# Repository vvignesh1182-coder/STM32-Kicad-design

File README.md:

# STM32 2-Layer PCB Design

A custom 2-layer Printed Circuit Board (PCB) designed around the STM32 microcontroller. This repository contains the complete open-source hardware files, schematics, PCB layouts, and manufacturing outputs created using **KiCad**.

---

## 📌 Project Overview
This project focuses on robust hardware layout practices for embedded microcontrollers, featuring optimized power distribution, ground copper pour zones, and signal integrity routing tailored for a standard 2-layer manufacturing stackup.

---

## 🚀 Key Features
* **Microcontroller Core:** Built around the STM32 MCU family for high-performance embedded control.
* **Power & Filtering:** Stable regulated power distribution featuring $+3.3\text{V}$ traces and ferrite bead isolation (`FB1`) to minimize noise between digital and analog domains.
* **Copper Ground Pour:** Utilizes dedicated GND copper fill zones and ground stitching vias to ensure low-impedance return paths and mitigate EMI.
* **Design Verification:** Fully verified and DRC-clean (Design Rules Checker) with confirmed schematic-to-layout parity.

---

## 📂 Repository Structure
```text
├── Schematic/       # KiCad schematic files (.kicad_sch) and symbol libraries
├── PCB/             # Board layout files (.kicad_pcb) and stackup settings
├── Manufacturing/   # Gerber files, drill files, and Bill of Materials (BOM) for fabrication
└── README.md        # Project documentation

🛠️ Tools & Requirements
Design Software: KiCad (v8.0 or compatible version recommended)

⚙️ Getting Started
Clone the repository:

Bash
git clone [https://github.com/vvignesh1182-coder/STM32-Kicad-design.git](https://github.com/vvignesh1182-coder/STM32-Kicad-design.git)
Open KiCad, select File > Open Project, and choose the .kicad_pro file from the repository directory.

Explore the Schematic Editor or PCB Editor to inspect the routing, stackup, and component placement.

📦 Manufacturing Outputs
The Manufacturing/ folder contains all necessary files ready to be zipped and uploaded directly to standard PCB fabrication houses (such as JLCPCB or PCBWay):

Gerber files (Copper layers, silkscreen, mask, edge cuts)

Excellon Drill files

Bill of Materials (BOM) CSV file

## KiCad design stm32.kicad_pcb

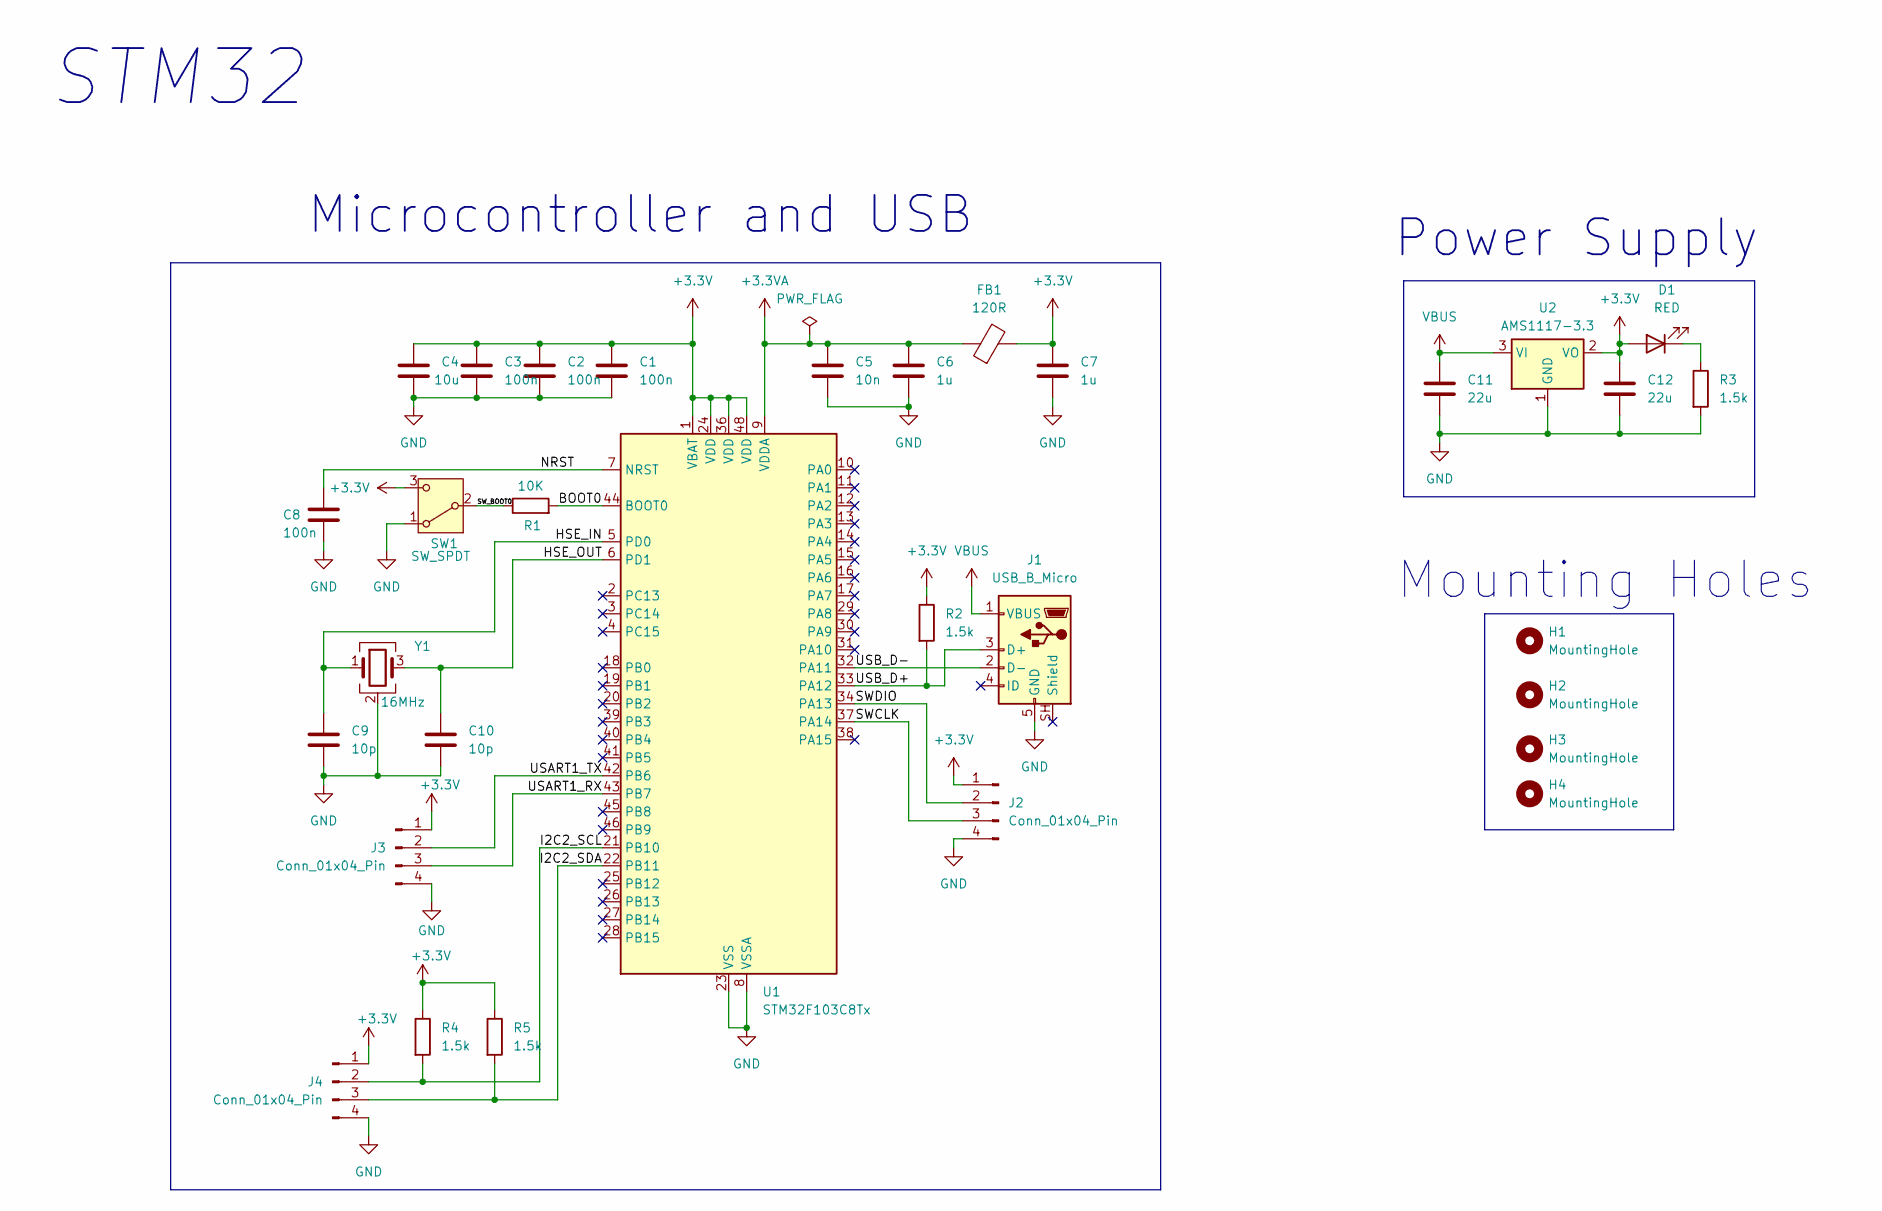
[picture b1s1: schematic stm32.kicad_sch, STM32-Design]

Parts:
C1, C2, C3, C8: 100n; C_0402_1005Metric
C4: 10u; C_0603_1608Metric
C5: 10n; C_0603_1608Metric
C6, C7: 1u; C_0402_1005Metric
C9, C10: 10p; C_0402_1005Metric
C11, C12: 22u; C_0805_2012Metric
D1: RED; LED_0603_1608Metric
FB1: 120R; L_0201_0603Metric
H1, H2, H3, H4: MountingHole; MountingHole_2.2mm_M2
J1: USB_B_Micro; USB_Micro-B_Wuerth_629105150521
J2, J3, J4: Conn_01x04_Pin; PinHeader_1x04_P2.54mm_Vertical
R1: 10K; R_0402_1005Metric
R2, R3, R4, R5: 1.5k; R_0402_1005Metric
SW1: SW_SPDT; SW_Slide_SPDT_Angled_CK_OS102011MA1Q
U1: STM32F103C8Tx; LQFP-48_7x7mm_P0.5mm
U2: AMS1117-3.3; SOT-223-3_TabPin2
Y1: 16MHz; Crystal_SMD_3225-4Pin_3.2x2.5mm

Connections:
+3.3V: C1.2, C2.2, C3.2, C4.2, C7.1, C12.1, D1.2 (A), FB1.2, J2.1, J3.1, J4.1, R2.1, R4.1, R5.1, SW1.3 (C), U1.1 (VBAT), U1.24 (VDD), U1.36 (VDD), U1.48 (VDD), U2.2 (VO)
+3.3VA: C5.1, C6.1, FB1.1, U1.9 (VDDA)
/BOOT0: R1.2, U1.44 (BOOT0)
/HSE_IN: C9.1, U1.5 (PD0), Y1.1
/HSE_OUT: C10.1, U1.6 (PD1), Y1.3
/I2C2_SCL: J4.2, R4.2, U1.21 (PB10)
/I2C2_SDA: J4.3, R5.2, U1.22 (PB11)
/NRST: C8.2, U1.7 (NRST)
/SWCLK: J2.3, U1.37 (PA14)
/SWDIO: J2.2, U1.34 (PA13)
/SW_BOOT0: R1.1, SW1.2 (B)
/USART1_RX: J3.3, U1.43 (PB7)
/USART1_TX: J3.2, U1.42 (PB6)
/USB_D+: J1.3 (D+), R2.2, U1.33 (PA12)
/USB_D-: J1.2 (D-), U1.32 (PA11)
GND: C1.1, C2.1, C3.1, C4.1, C5.2, C6.2, C7.2, C8.1, C9.2, C10.2, C11.2, C12.2, J1.5 (GND), J2.4, J3.4, J4.4, R3.2, SW1.1 (A), U1.8 (VSSA), U1.23 (VSS), U1.35 (VSS), U1.47 (VSS), U2.1 (GND), Y1.2 (G), Y1.4 (G)
unnamed: D1.1 (K), R3.1
VBUS: C11.1, J1.1 (VBUS), U2.3 (VI)

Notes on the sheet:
Mounting Holes
Power Supply
Microcontroller and USB
STM32

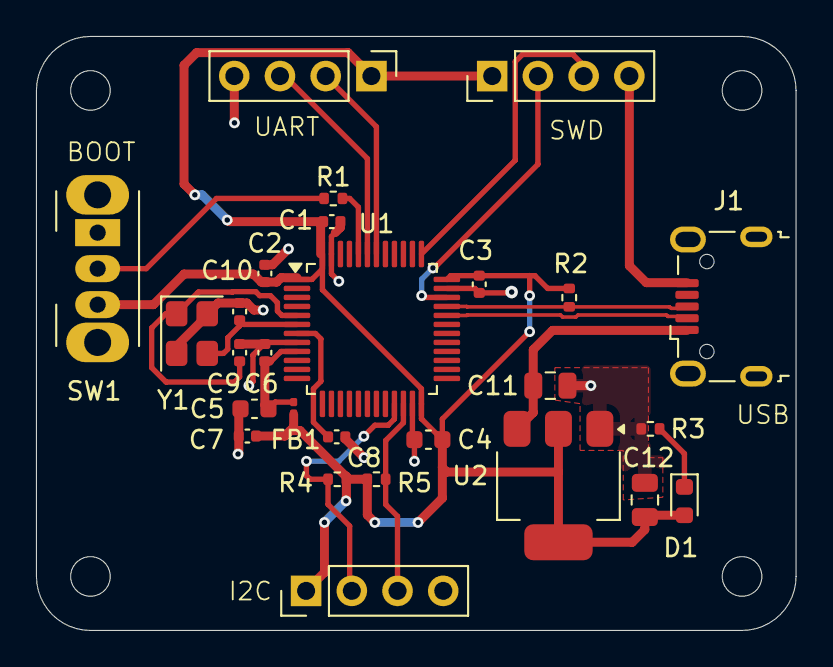
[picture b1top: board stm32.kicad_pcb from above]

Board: 2 copper layers, 42.2 x 33.0 mm, 31 parts (0 on the bottom side), 18 nets.
